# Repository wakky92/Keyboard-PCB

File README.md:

# Keyboard-PCB
A simple barebones PCB for a mechanical keyboard using KICAD.

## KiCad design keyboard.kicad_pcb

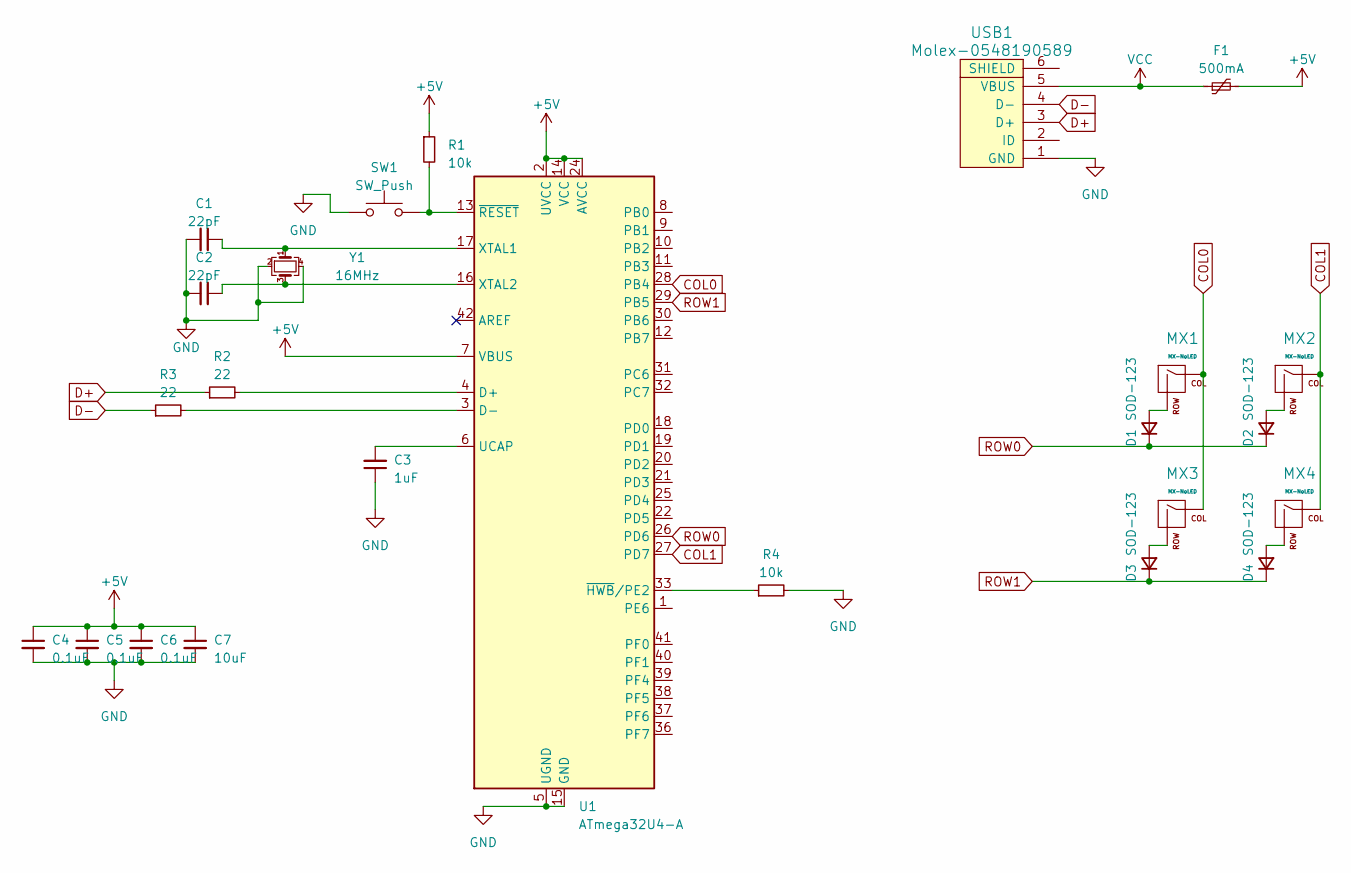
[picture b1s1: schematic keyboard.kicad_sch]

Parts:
C1, C2: 22pF; C_0805_2012Metric
C3: 1uF; C_0805_2012Metric
C4, C5, C6: 0.1uF; C_0805_2012Metric
C7: 10uF; C_0805_2012Metric
D1, D2, D3, D4: SOD-123; D_SOD-123
F1: 500mA; Fuse_1206_3216Metric
MX1, MX2, MX3, MX4: MX-NoLED; MX-1U
R1, R4: 10k; R_0805_2012Metric
R2, R3: 22; R_0805_2012Metric
SW1: SW_Push; SKQG-1155865
U1: ATmega32U4-A; TQFP-44_10x10mm_P0.8mm
USB1: Molex-0548190589
Y1: 16MHz; Crystal_SMD_3225-4Pin_3.2x2.5mm

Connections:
+5V: C4.1, C5.1, C6.1, C7.1, F1.2, R1.1, U1.2 (UVCC), U1.7 (VBUS), U1.14 (VCC), U1.24 (AVCC), U1.34 (VCC), U1.44 (AVCC)
COL0: MX1.1 (COL), MX3.1 (COL), U1.28 (PB4)
COL1: MX2.1 (COL), MX4.1 (COL), U1.27 (PD7)
D+: R2.1, USB1.3 (D+)
D-: R3.1, USB1.4 (D-)
GND: C1.2, C2.2, C3.1, C4.2, C5.2, C6.2, C7.2, R4.2, SW1.1, U1.5 (UGND), U1.15 (GND), U1.23 (GND), U1.35 (GND), U1.43 (GND), USB1.1 (GND), Y1.2, Y1.4
unnamed: D1.2 (A), MX1.2 (ROW)
unnamed: D2.2 (A), MX2.2 (ROW)
unnamed: D3.2 (A), MX3.2 (ROW)
unnamed: D4.2 (A), MX4.2 (ROW)
unnamed: R2.2, U1.4 (D+)
unnamed: R3.2, U1.3 (D-)
unnamed: C3.2, U1.6 (UCAP)
unnamed: C1.1, U1.17 (XTAL1), Y1.1
unnamed: C2.1, U1.16 (XTAL2), Y1.3
unnamed: R4.1, U1.33 (~HWB/PE2)
unnamed: R1.2, SW1.2, U1.13 (~RESET)
ROW0: D1.1 (K), D2.1 (K), U1.26 (PD6)
ROW1: D3.1 (K), D4.1 (K), U1.29 (PB5)
VCC: F1.1, USB1.5 (VBUS)

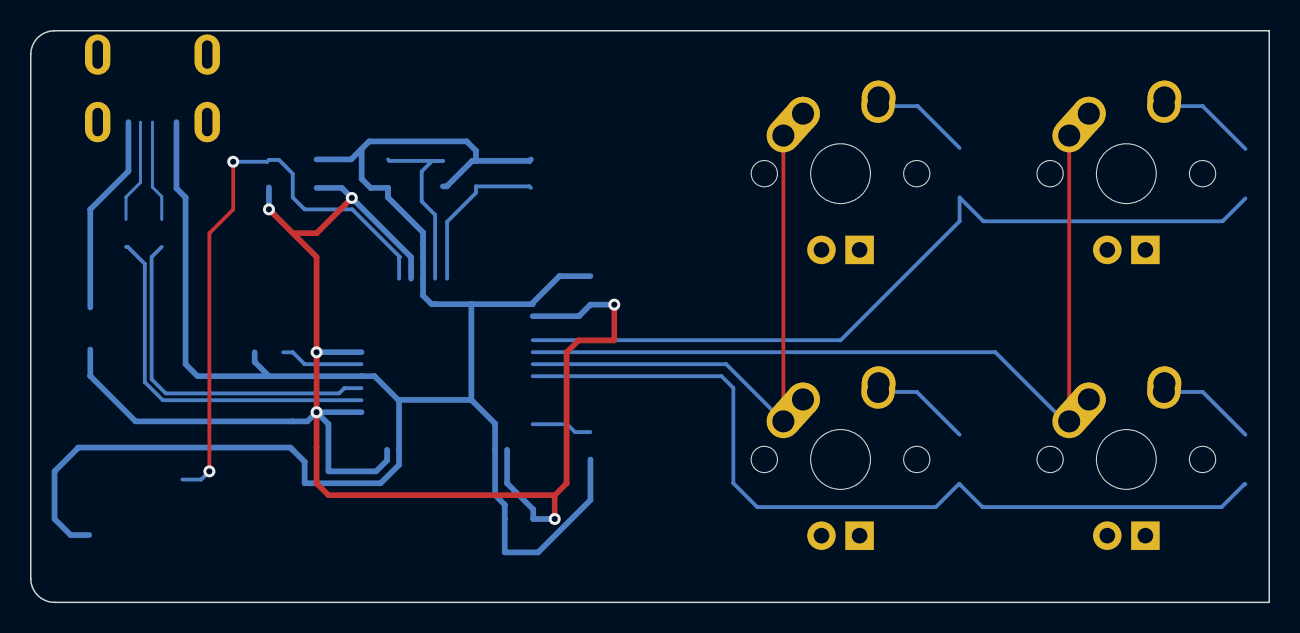
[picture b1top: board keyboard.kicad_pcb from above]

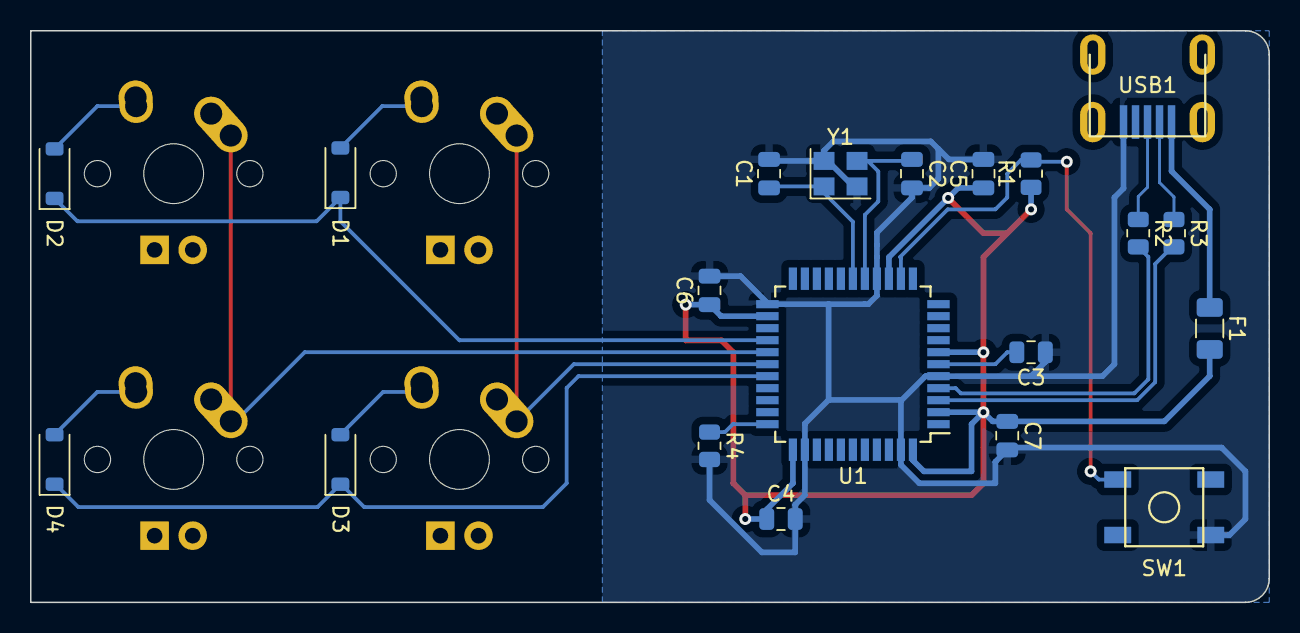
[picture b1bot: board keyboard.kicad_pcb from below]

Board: 2 copper layers, 82.6 x 38.1 mm, 24 parts (20 on the bottom side), 20 nets.

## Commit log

2023-09-12 added from pc
    KICAD
